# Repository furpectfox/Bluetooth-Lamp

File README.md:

# Bluetooth-Lamp
A floor lamp controlled with your smartphone via bluetooth

## Schematic
[Flyback Converter Circuit](KiCad/BLE_Lamp-Flyback_Converter.pdf)

[Bluetooth Circuit](KiCad/BLE_Lamp.pdf)

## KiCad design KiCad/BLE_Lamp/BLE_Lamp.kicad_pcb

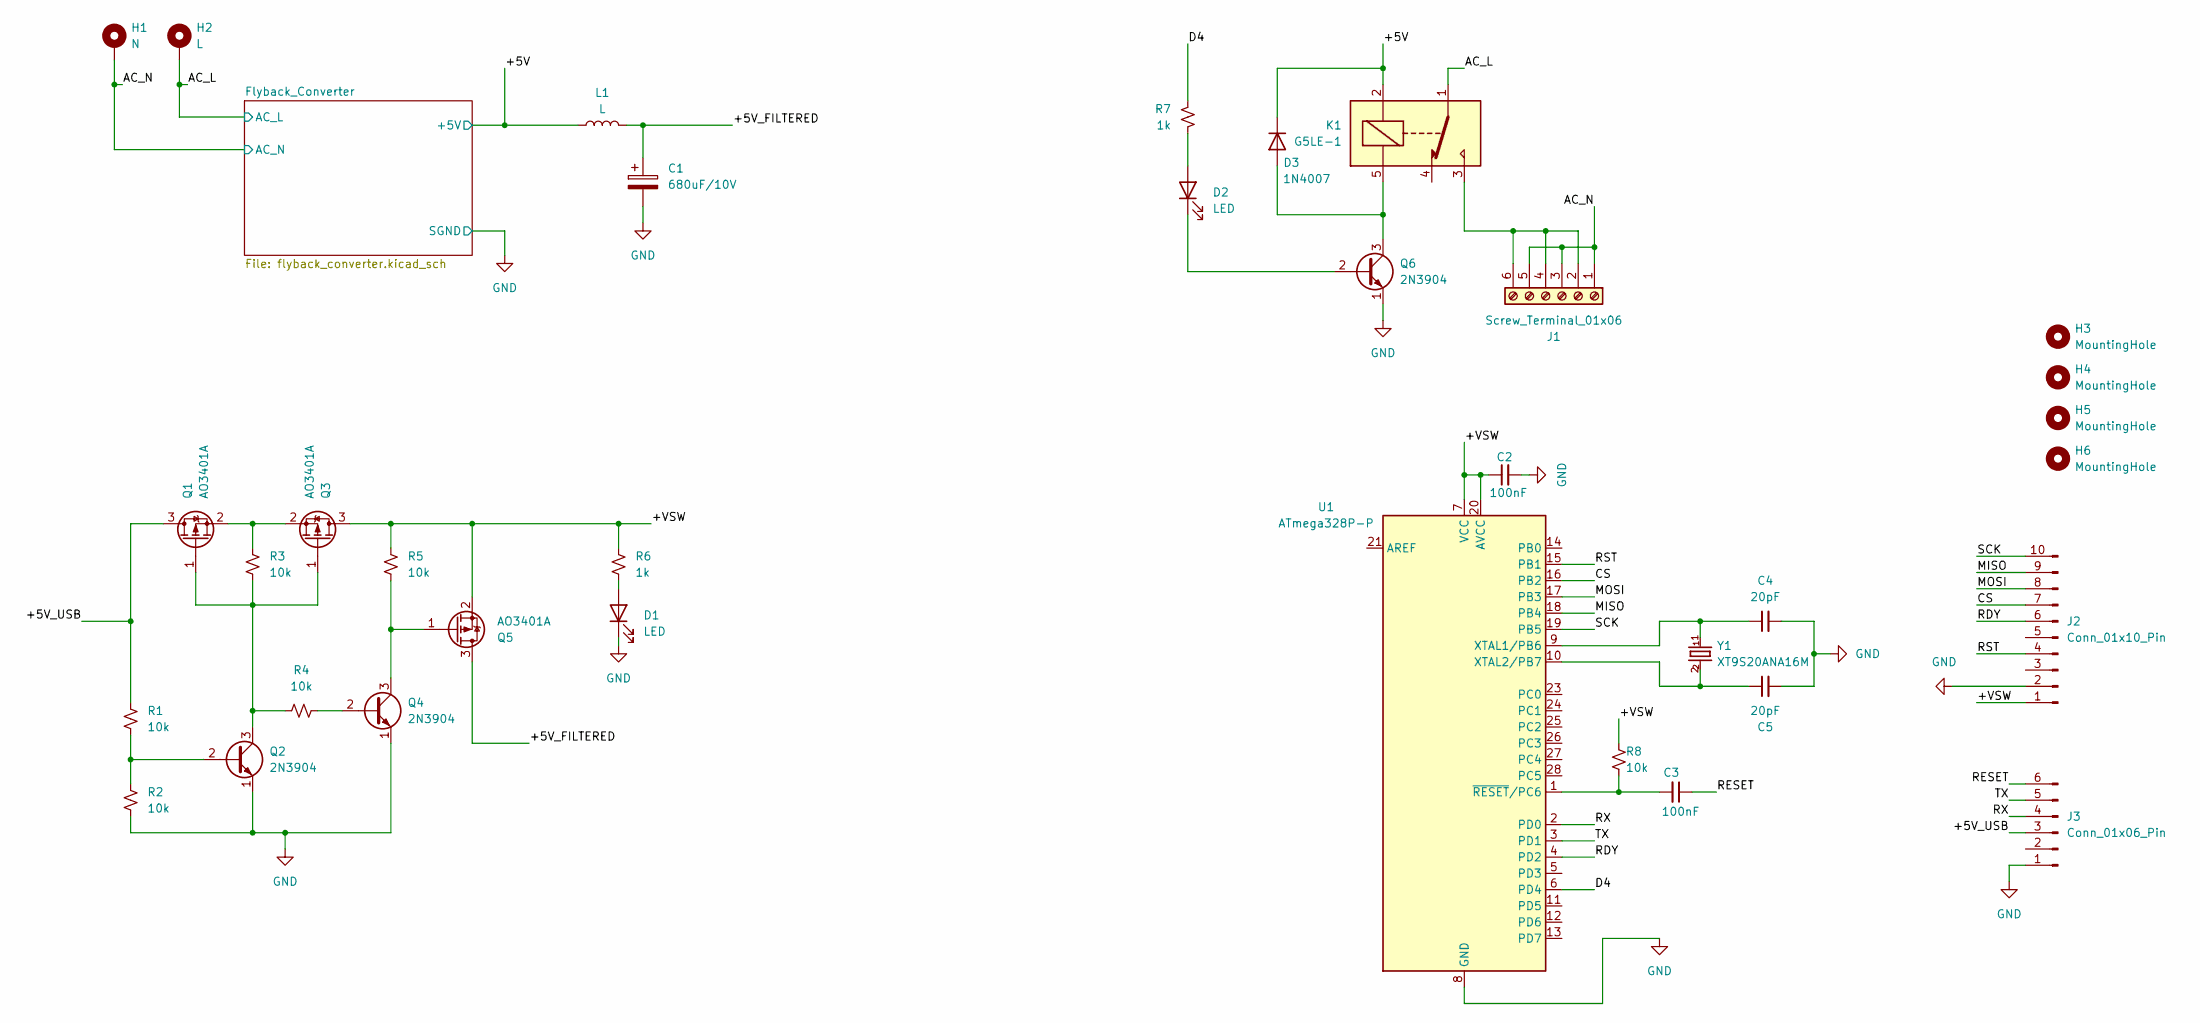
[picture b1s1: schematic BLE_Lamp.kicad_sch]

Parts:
C1: 680uF/10V; CP_Radial_D8.0mm_P3.80mm
C2, C3: 100nF; C_0603_1608Metric_Pad1.08x0.95mm_HandSolder
C4, C5: 20pF; C_Disc_D5.1mm_W3.2mm_P5.00mm
D1, D2: LED; LED_0603_1608Metric_Pad1.05x0.95mm_HandSolder
D3: 1N4007; D_SOD-123F
H1: N; SolderWire-0.75sqmm_1x01_D1.25mm_OD3.5mm_Relief
H2: L; SolderWire-0.75sqmm_1x01_D1.25mm_OD3.5mm_Relief
H3, H4, H5, H6: MountingHole; MountingHole_3.2mm_M3_Pad
J1: Screw_Terminal_01x06; TerminalBlock_MaiXu_MX126-5.0-06P_1x06_P5.00mm
J2: Conn_01x10_Pin; PinHeader_1x10_P2.54mm_Vertical
J3: Conn_01x06_Pin; PinHeader_1x06_P2.54mm_Vertical
K1: G5LE-1; Relay_SPDT_Omron-G5LE-1
L1: L; L_Toroid_Vertical_L10.0mm_W5.0mm_P5.08mm
Q1, Q3, Q5: AO3401A; SOT-23_Handsoldering
Q2, Q4, Q6: 2N3904; SOT-23_Handsoldering
R1, R2, R3, R4, R5, R8: 10k; R_0603_1608Metric_Pad0.98x0.95mm_HandSolder
R6, R7: 1k; R_0603_1608Metric_Pad0.98x0.95mm_HandSolder
U1: ATmega328P-P; DIP-28_W7.62mm
Y1: XT9S20ANA16M; XTAL_XT9S20ANA16M

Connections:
/+5V: D3.1 (K), K1.2, L1.1; also elsewhere on the board
/+5V_FILTERED: C1.1, L1.2, Q5.3 (D)
/+5V_USB: J3.3, Q1.3 (D), R1.1
/+VSW: C2.1, J2.1, Q3.3 (D), Q5.2 (S), R5.1, R6.1, R8.1, U1.7 (VCC), U1.20 (AVCC)
/AC_L: H2.1, K1.1; also elsewhere on the board
/AC_N: H1.1, J1.1, J1.3, J1.5; also elsewhere on the board
/CS: J2.7, U1.16 (PB2)
/D4: R7.1, U1.6 (PD4)
/MISO: J2.9, U1.18 (PB4)
/MOSI: J2.8, U1.17 (PB3)
/RDY: J2.6, U1.4 (PD2)
/RESET: C3.1, J3.6
/RST: J2.4, U1.15 (PB1)
/RX: J3.4, U1.2 (PD0)
/SCK: J2.10, U1.19 (PB5)
/TX: J3.5, U1.3 (PD1)
GND: C1.2, C2.2, C4.2, C5.2, D1.1 (K), J2.2, J3.1, Q2.1 (E), Q4.1 (E), Q6.1 (E), R2.2, U1.8 (GND), U1.22 (GND); also elsewhere on the board
unnamed: D1.2 (A), R6.2
unnamed: D2.2 (A), R7.2
unnamed: D2.1 (K), Q6.2 (B)
unnamed: D3.2 (A), K1.5, Q6.3 (C)
unnamed: J1.2, J1.4, J1.6, K1.3
unnamed: Q1.1 (G), Q2.3 (C), Q3.1 (G), R3.2, R4.1
unnamed: Q1.2 (S), Q3.2 (S), R3.1
unnamed: Q2.2 (B), R1.2, R2.1
unnamed: Q4.2 (B), R4.2
unnamed: Q4.3 (C), Q5.1 (G), R5.2
unnamed: C4.1, U1.9 (XTAL1/PB6), Y1.1
unnamed: C5.1, U1.10 (XTAL2/PB7), Y1.2
unnamed: C3.2, R8.2, U1.1 (~RESET/PC6)

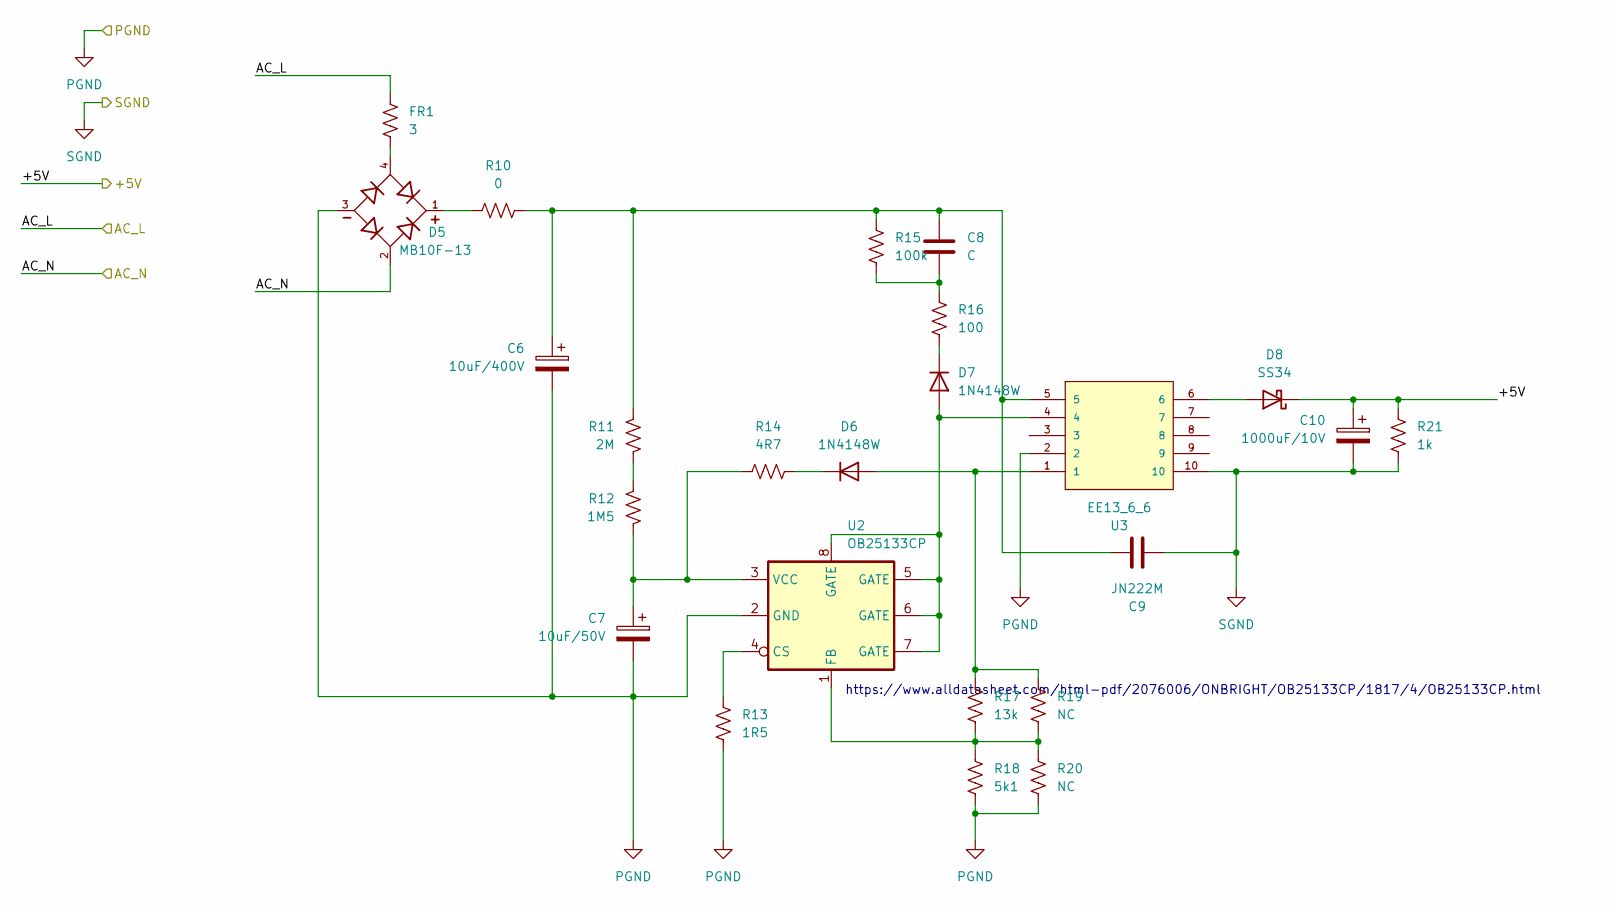
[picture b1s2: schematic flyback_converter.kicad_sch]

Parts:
C6: 10uF/400V; CP_Radial_D8.0mm_P3.80mm
C7: 10uF/50V; CP_Radial_D5.0mm_P2.00mm
C8: C; C_0805_2012Metric_Pad1.18x1.45mm_HandSolder
C9: JN222M; C_Disc_D10.5mm_W5.0mm_P10.00mm
C10: 1000uF/10V; CP_Radial_D8.0mm_P3.80mm
D5: MB10F-13; DIOB_MB10F-13; PARTREV 3 - 2
D6, D7: 1N4148W; D_SOD-123
D8: SS34; D_SMA
FR1: 3; R_Axial_DIN0309_L9.0mm_D3.2mm_P15.24mm_Horizontal
R10: 0; R_1206_3216Metric_Pad1.30x1.75mm_HandSolder
R11: 2M; R_1206_3216Metric_Pad1.30x1.75mm_HandSolder
R12: 1M5; R_1206_3216Metric_Pad1.30x1.75mm_HandSolder
R13: 1R5; R_1206_3216Metric_Pad1.30x1.75mm_HandSolder
R14: 4R7; R_0805_2012Metric_Pad1.20x1.40mm_HandSolder
R15: 100k; R_0805_2012Metric_Pad1.20x1.40mm_HandSolder
R16: 100; R_0805_2012Metric_Pad1.20x1.40mm_HandSolder
R17: 13k; R_0805_2012Metric_Pad1.20x1.40mm_HandSolder
R18: 5k1; R_0805_2012Metric_Pad1.20x1.40mm_HandSolder
R19, R20: NC; R_0805_2012Metric_Pad1.20x1.40mm_HandSolder
R21: 1k; R_0805_2012Metric_Pad1.20x1.40mm_HandSolder
U2: OB25133CP; SOIC-8_3.9x4.9mm_P1.27mm
U3: EE13_6_6; BOBBIN_EE13_6_6; PARTREV 11/19

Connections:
/+5V: C10.1, D8.1 (K), R21.1; also elsewhere on the board
/AC_L: FR1.2; also elsewhere on the board
/AC_N: D5.2; also elsewhere on the board
GND: C9.1, C10.2, R21.2, U3.10; also elsewhere on the board
unnamed: C6.1, C8.1, C9.2, R10.2, R11.2, R15.1, U3.5
unnamed: C8.2, R15.2, R16.1
unnamed: D5.1, R10.1
unnamed: D5.4, FR1.1
unnamed: D6.2 (A), R17.1, R19.1, U3.1
unnamed: D6.1 (K), R14.1
unnamed: D7.2 (A), U2.5 (GATE), U2.6 (GATE), U2.7 (GATE), U2.8 (GATE), U3.4
unnamed: D7.1 (K), R16.2
unnamed: D8.2 (A), U3.6
unnamed: R11.1, R12.2
unnamed: R13.2, U2.4 (CS)
unnamed: R17.2, R18.1, R19.2, R20.1, U2.1 (FB)
unnamed: C7.1, R12.1, R14.2, U2.3 (VCC)
PGND: C6.2, C7.2, D5.3, R13.1, R18.2, R20.2, U2.2 (GND), U3.2

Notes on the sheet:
https://www.alldatasheet.com/html-pdf/2076006/ONBRIGHT/OB25133CP/1817/4/OB25133CP.html

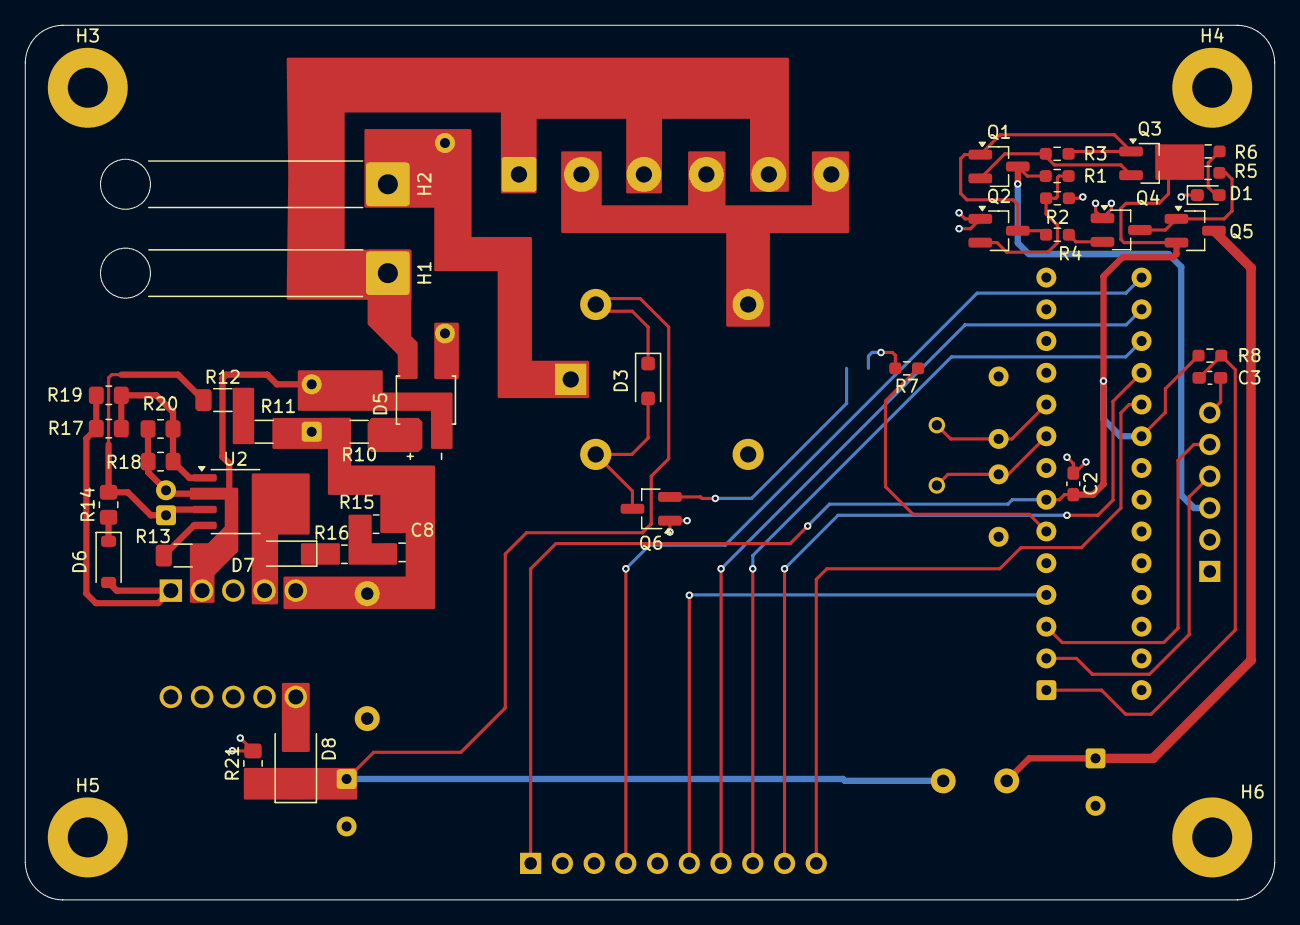
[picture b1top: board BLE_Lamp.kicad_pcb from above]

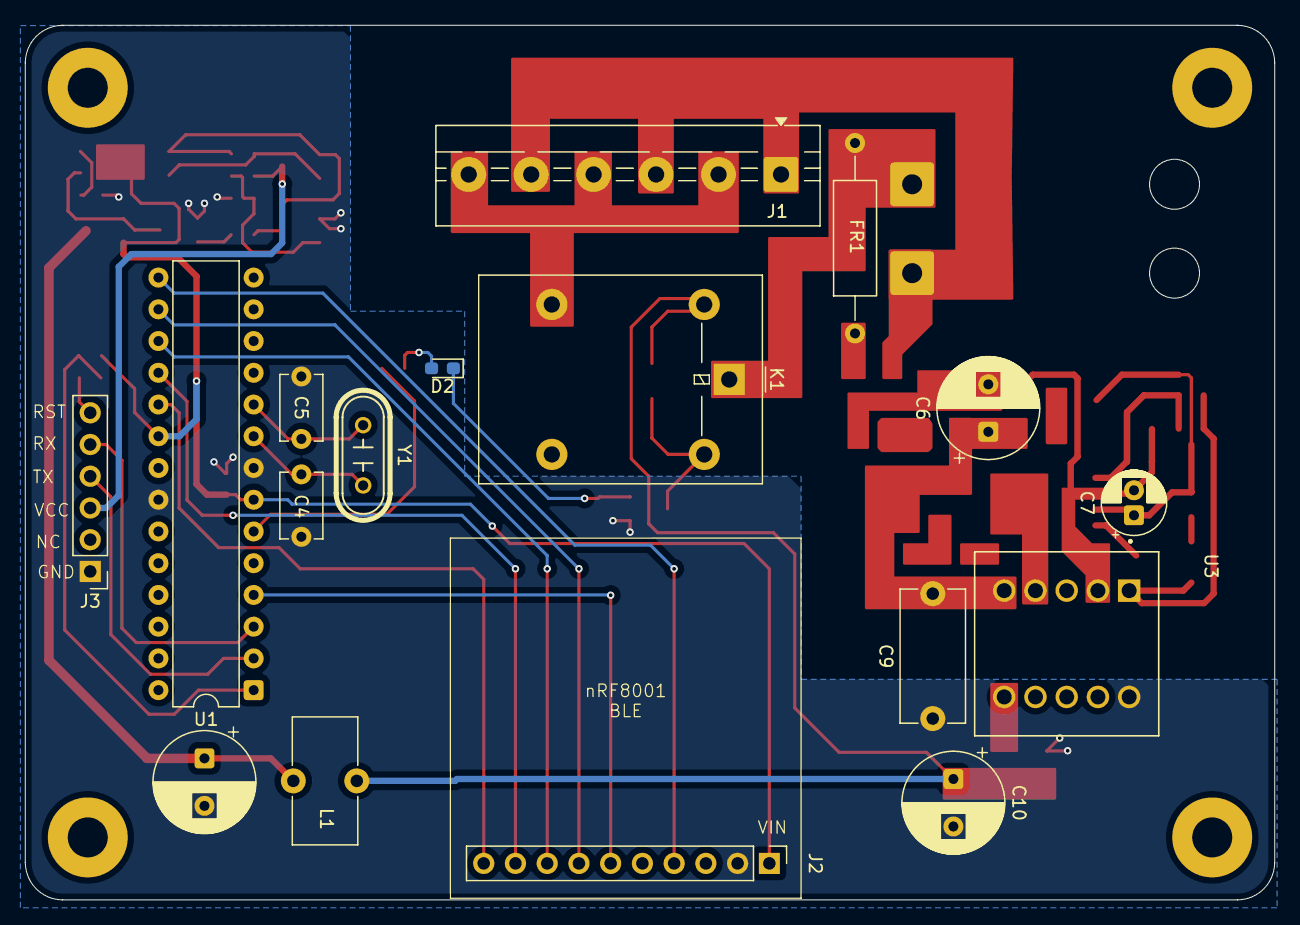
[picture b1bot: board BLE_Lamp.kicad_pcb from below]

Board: 2 copper layers, 100.0 x 70.0 mm, 59 parts (17 on the bottom side), 44 nets.

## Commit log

2025-12-28 add project files
2025-12-28 add images
